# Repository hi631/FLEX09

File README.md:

<p><b><font size="+1"><span class="VIiyi" jsaction="mouseup:BR6jm" jsname="jqKxS" lang="en" style="-webkit-tap-highlight-color: transparent; display: inline; color: rgb(0, 0, 0); font-family: Roboto, RobotoDraft, Helvetica, Arial, sans-serif; font-size: 24px; font-style: normal; font-variant-ligatures: normal; font-variant-caps: normal; font-weight: 400; letter-spacing: normal; orphans: 2; text-align: start; text-indent: 0px; text-transform: none; white-space: pre-wrap; widows: 2; word-spacing: 0px; -webkit-text-stroke-width: 0px; background-color: rgb(245, 245, 245); text-decoration-thickness: initial; text-decoration-style: initial; text-decoration-color: initial;"><span jsaction="agoMJf:PFBcW;usxOmf:aWLT7;jhKsnd:P7O7bd,F8DmGf;Q4AGo:Gm7gYd,qAKMYb;uFUCPb:pvnm0e,pfE8Hb,PFBcW;f56efd:dJXsye;EnoYf:KNzws,ZJsZZ,JgVSJc;zdMJQc:cCQNKb,ZJsZZ,zchEXc;Ytrrj:JJDvdc;tNR8yc:GeFvjb;oFN6Ye:hij5Wb" jscontroller="Zl5N8" jsmodel="SsMkhd" jsname="txFAF" class="JLqJ4b ChMk0b" data-language-for-alternatives="en" data-language-to-translate-into="ja" data-phrase-index="0" jsdata="uqLsIf;_;$7" style="-webkit-tap-highlight-color: transparent; cursor: pointer;"><span jsaction="click:qtZ4nf,GFf3ac,tMZCfe; contextmenu:Nqw7Te,QP7LD; mouseout:Nqw7Te; mouseover:qtZ4nf,c2aHje" jsname="W297wb" style="-webkit-tap-highlight-color: transparent;">Make 6809 with FPGA and run FLEX</span></span></span><span style="color: rgb(0, 0, 0); font-family: Roboto, RobotoDraft, Helvetica, Arial, sans-serif; font-size: 24px; font-style: normal; font-variant-ligatures: normal; font-variant-caps: normal; font-weight: 400; letter-spacing: normal; orphans: 2; text-align: start; text-indent: 0px; text-transform: none; white-space: pre-wrap; widows: 2; word-spacing: 0px; -webkit-text-stroke-width: 0px; background-color: rgb(245, 245, 245); text-decoration-thickness: initial; text-decoration-style: initial; text-decoration-color: initial; display: inline !important; float: none;"> </span></font></b></p>
<p><font size="+1">#Simulator (SIM6809)</font><br>
<a>original material</a>[<a href="https://github.com/gordonjcp/sim6809">SIM6809</a>]<br>
SIM6809 is compiled with MINGW32.<br>
Start MINGW32 and move to the source directory with &quot;cd / C / ...... / sim6809&quot;,<br>
Compile with one make, start with &quot;./sim6809&quot; and the prompt should appear.<br>
<br>
<font size="+1"># FLEX</font><br>
Portable by adding serial and SD drivers to DRIVER (file is CONSOLE).<br>
The OS is localized to  $ C000-  $ FFFF, and it may not be possible to
move. The user area is 48KB.<br>
Add necessary processing (input / output) and check the operation of the assembled HEX with the simulator.<br>
<br>
There is a sample of access to the SD card at [<a href="https://github.com/nealcrook/multicomp6809">MULTICOMP6809</a>].<br>
However, FLEX has 256 bytes / sector, while SD card has 512 bytes / sector.<br>
The sample was a method that did not use half of the 512 bytes, but it was divided R / W using a buffer.<br>
<br>
Batch job &quot;_flex_SIM.bat&quot; creates HEX for the simulator.<br>
* Drive is R / W for files on Windows.<br>
Batch job &quot;_flex_FPGA.bat&quot; creates HEX for FPGA.<br>
* The drive is R / W by dividing the SD card.<br>
<br>
Furthermore, since it does not work under windows already, use an extender called msdos.exe.<br>
[<a href="http://takeda-toshiya.my.coocan.jp/msdos/">MS-DOS Player for Win32-x64</a>] <br>
<br>
<font size="+1"># FPGA6809 hard</font><br>
It would be easier to understand the configuration by looking at [<a href="http://searle.x10host.com/Multicomp/index.html">Grant's MULTICOMP</a>].<br>
* Almost as it is. However, VHDL is converted to verilog.<br>
6809 is operating at 30MHz.<br>
The SD card gives the driver 20MHz, so it probably works at 10MHz.<br>
<br>
Green is EP2C5 mounted board, black and big is FPGA<br>
The board on it is a board with RAM and SD made by CNC<br>
The lower right is the serial board (commercially available FTD1232)<br>
The upper right is the VGA output and PS2 input board (not connected in this software)<br>
<br>
<font size="+1">#FPGA6809 software</font><br>
The software can be compiled with quartus II.<br>
EP2C5 is an old generation Cyclone II, so be careful as it can only be compiled before 13.0sp1.<br>
1. If you want to run BASIC, assemble basic.asm.<br>
2. If you want to run monitor, assemble monitor.asm.<br>
* Both generate basic.hex, so there is no need to change the verilog side.<br>
<br>
<font size="+1">#Monitor program</font><br>
Used for starting FLEX and debugging when FLEX does not start.<br>
Starting FLEX is<br>
1. After starting the monitor, press'B'+'Ret' to start. (Pre-setting required)<br>
2. It is also possible to start from BASIC, and'%' is displayed by'Ctrl' +'L', so copy and paste the FLEX HEX file on the screen.<br>
Automatically start after the message &quot;% %%% ...&quot; is displayed<br>
* It is assumed that basic.asm (modified version) under the moni09 directory is used. It will be started from \ $ C400.<br>
The monitor is localized in two places,  $ E000 and \  A000, and starts
as  $ A000 at the time of reset.<br>
After copying itself to the RAM of \  A000, invalidate the ROM and free
up the FLEX load area.<br>
<br>
<font size="+1">#Drive layout on SD card</font><br>
0000-059F drive 0<br>
05A0 --05CF boot loader<br>
0800-0D9F drive 1<br>
1000-159F drive 2<br>
1800-1D9F drive 3<br>
* Described as 512B / S<br>
* 4 units can be selected, but the 4th unit cannot be used. (I feel like it's 3 in FLEX)<br>
For Card Day, use the command as shown below to combine the disks and write to SD with win32diskimager.<br>
Copy /b FLEX9SYS.DSK + DUMY_4CKFF.bin + BLANK.DSK + DUMY_4CKFF.bin + BLANK.DSK + DUMY_4CKFF.bin SD4M.img<br>
* Obtain FLEX9SYS.DSK from [<a href="http://www.evenson-consulting.com/swtpc/">SWTPC</a>]. I don't think there were any particular restrictions on use.<br>
<br>
<br>
<font size="+1">#Boot loader settings</font><br>
1. The monitor starts by resetting.<br>
2. Issue the'L'command. Check the'%' display.Copy and paste <br>
3.flex9.hexe to the terminal and load it into memory. (Written to $ C000-
$ FFFF)<br>
4. Issue a write command with'W 5001 C000 3F'.<br>
* 5001 is equivalent to  $ 800 sector (512B / S conversion) on the card.<br>
5. Confirm the operation with the'B'command.<br>
<br>
<a href="https://qiita.com/hi631/items/5b386fb230afcc87c66d">Here is</a> a little more detailed explanation (but in Japanese) <br>
<br>
</p>

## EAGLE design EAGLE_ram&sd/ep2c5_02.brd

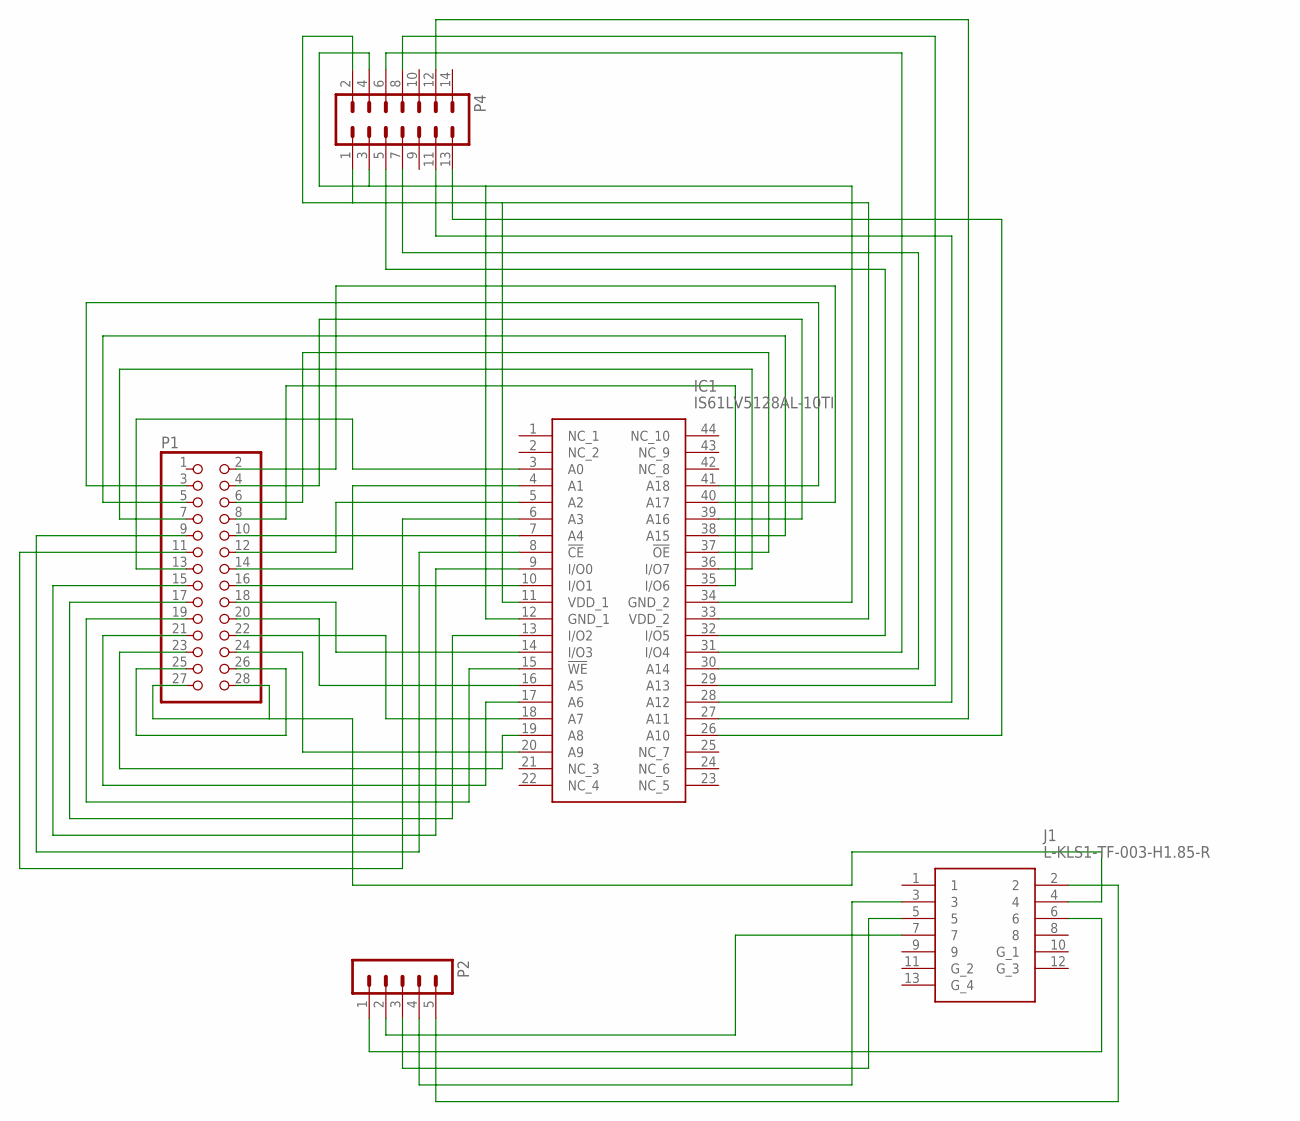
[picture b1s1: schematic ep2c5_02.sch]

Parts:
IC1: IS61LV5128AL-10TI; SOP80P1176X120-44N
J1: L-KLS1-TF-003-H1.85-R
P1: PINHD-2X14; 2X14
P2: MA05-1
P4: MA07-2

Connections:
unnamed: J1.4, P1.27, P1.28
unnamed: IC1.20 (A9), P1.24
unnamed: P1.25, P1.26
unnamed: IC1.19 (A8), P1.23
unnamed: IC1.18 (A7), P1.22
unnamed: IC1.17 (A6), P1.21
unnamed: IC1.16 (A5), P1.20
unnamed: IC1.15 (!WE), P1.19
unnamed: IC1.14 (I/O3), P1.18
unnamed: IC1.13 (I/O2), P1.17
unnamed: IC1.10 (I/O1), P1.16
unnamed: IC1.9 (I/O0), P1.15
unnamed: IC1.12 (GND_1), IC1.34 (GND_2), P4.3, P4.4
unnamed: IC1.8 (!CE), P1.9
unnamed: IC1.7 (A4), P1.10
unnamed: IC1.6 (A3), P1.11
unnamed: IC1.4 (A1), P1.14
unnamed: IC1.3 (A0), P1.13
unnamed: IC1.35 (I/O6), P1.8
unnamed: IC1.36 (I/O7), P1.7
unnamed: IC1.11 (VDD_1), IC1.33 (VDD_2), P4.1, P4.2
unnamed: IC1.37 (!OE), P1.6
unnamed: IC1.38 (A15), P1.5
unnamed: IC1.39 (A16), P1.4
unnamed: IC1.41 (A18), P1.3
unnamed: IC1.40 (A17), P1.2
unnamed: IC1.32 (I/O5), P4.5
unnamed: IC1.31 (I/O4), P4.6
unnamed: IC1.30 (A14), P4.7
unnamed: IC1.29 (A13), P4.8
unnamed: IC1.28 (A12), P4.11
unnamed: IC1.27 (A11), P4.12
unnamed: IC1.26 (A10), P4.13
unnamed: J1.7, P2.2
unnamed: J1.6, P2.1
unnamed: J1.5, P2.3
unnamed: J1.3, P2.4
unnamed: J1.2, P2.5
unnamed: IC1.5 (A2), P1.12

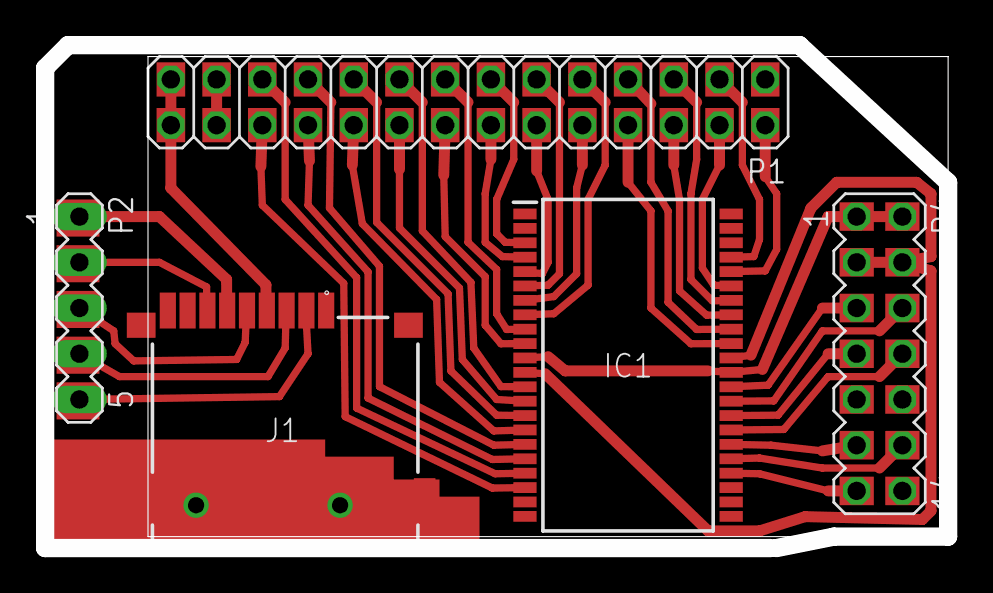
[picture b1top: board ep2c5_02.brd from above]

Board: 2 copper layers, 50.2 x 27.9 mm, 5 parts (0 on the bottom side), 39 nets.

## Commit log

2021-05-10 Add check
